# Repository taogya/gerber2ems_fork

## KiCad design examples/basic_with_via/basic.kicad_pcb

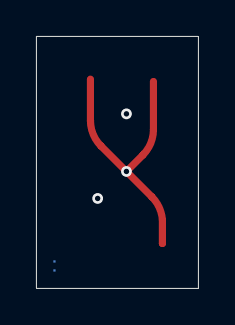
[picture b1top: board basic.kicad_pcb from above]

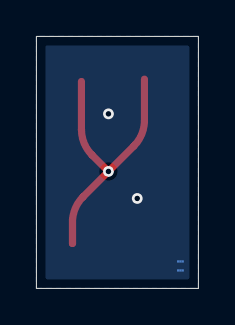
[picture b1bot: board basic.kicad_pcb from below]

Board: 2 copper layers, 9.0 x 14.0 mm, 7 parts (2 on the bottom side), 2 nets.

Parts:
SP1, SP2, SP3: Simulation_Port
TP1, TP2, TP3, TP4: Net-Tie_2; NetTie-2_SMD_Pad0.127mm

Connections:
/MSL: TP1.1, TP1.2, TP3.1, TP3.2
GND: TP2.1, TP2.2, TP4.1, TP4.2

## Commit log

2025-03-17 add example for top to bottom
2025-03-18 add with via

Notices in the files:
parts and their libraries:
License: Apache-2.0
